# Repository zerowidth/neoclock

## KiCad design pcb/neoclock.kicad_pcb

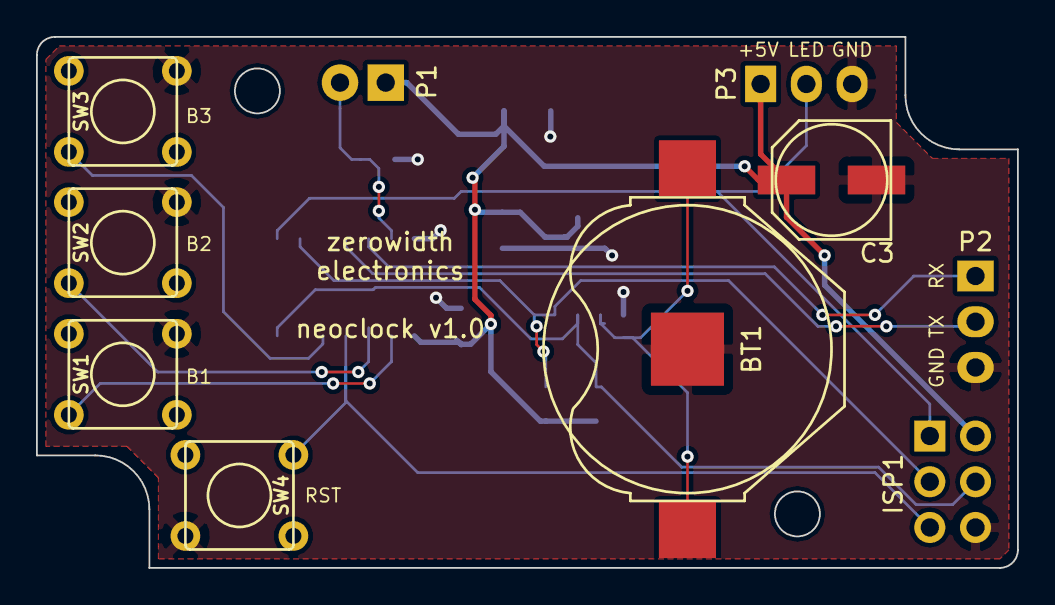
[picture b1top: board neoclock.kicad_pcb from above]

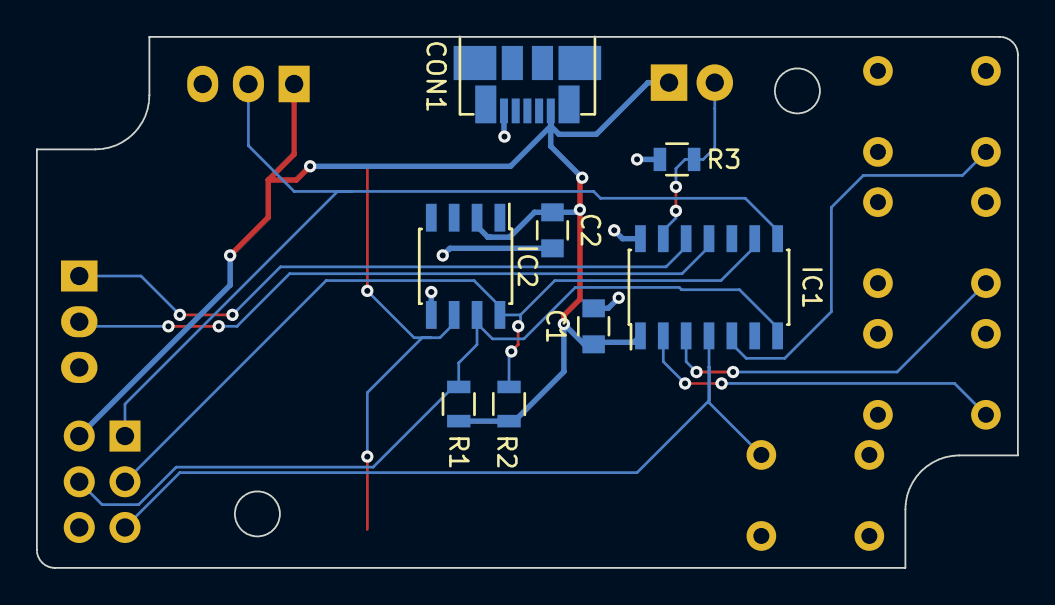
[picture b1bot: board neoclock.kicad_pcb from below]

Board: 2 copper layers, 54.5 x 29.5 mm, 18 parts (8 on the bottom side), 13 nets.

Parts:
BT1: CR1632; BAT_Keystone_3012TR_16mm
C1, C2: 0.1uF; C_0805
C3: 100uF; CP_Panasonic_SV_D
CON1: USB-MICRO-B; CONN_Molex_USB_Micro_SMT
IC1: ATTINY84-S; SOIC-14_3.9x8.7mm_Pitch1.27mm
IC2: DS3231MZ+; SOIC-8_3.9x4.9mm_Pitch1.27mm
ISP1: AVR-ISP-6; Pin_Header_Straight_2x03_Plain
P1: Photoresistor; Pin_Header_Straight_1x02_Plain
P2: Serial; Pin_Header_Straight_1x03_Plain
P3: NeoPixel Ring; Pin_Header_Straight_1x03_Plain
R1, R2, R3: 4.7k; R_0805
SW1: Button 1; BTN_E_Switch_TL1105
SW2: Button 2; BTN_E_Switch_TL1105
SW3: Button 3; BTN_E_Switch_TL1105
SW4: RESET; BTN_E_Switch_TL1105

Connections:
+5V: C1.1, C2.1, C3.1, CON1.1, IC1.1, IC2.2, ISP1.2, P1.1, P3.1, R1.1, R2.1
/BTN1: IC1.2, SW1.1
/BTN2: IC1.3, SW2.1
/BTN3: IC1.5, SW3.1
/LEDS: IC1.8, ISP1.1, P3.2
/LIGHT: IC1.13, P1.2, R3.1
/MOSI: IC1.7, IC2.7, ISP1.4, R1.2
/RST: IC1.4, ISP1.5, SW4.1
/RX: IC1.12, P2.1
/SCK: IC1.9, IC2.8, ISP1.3, R2.2
/TX: IC1.11, P2.2
/VBat: BT1.1, IC2.6
GND: BT1.2, C1.2, C2.2, C3.2, CON1.5, IC1.14, IC2.5, ISP1.6, P2.3, P3.3, R3.2, SW1.4, SW2.4, SW3.4, SW4.4

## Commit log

2015-02-12 Hello world: Blinking LED
    With Makefile from crosspack-avr
2015-02-13 Use attiny84a device
    The avr/io.h file has a more comprehensive set of constants e.g. timer
    control register bits. avrdude doesn't know about the -a variant though.
2015-02-13 `make all` compiles and flashes
    Also split out a `size` target for printing out the size
2015-02-13 PWM with FastPWM mode
2015-02-14 Import softuart library
    https://github.com/blalor/avr-softuart
2015-02-14 Get softuart demo up and running
2015-02-14 Remove -B argument from avrdude so it runs faster
    It might be needed again for flashing a new chip, though.
2015-02-14 Remove comments from makefile
2015-02-14 Add link-time optimization to build
    This cuts down the final build size by detecting undeclared static
    globals and more.
2015-02-14 Change suffix rule to prefix rule to build when headers change
    Previously, touching a header file wouldn't trigger a rebuild.
2015-02-14 Reintroduce PWM code
2015-02-14 Increase serial baud to 9600
2015-02-15 Fix dependency generation in Makefile
    -MMD generates local .d dependency files when compiling, and then the
    Makefile includes 'em to keep things updated.
2015-02-15 Generalize the PWM bits somewhat
2015-02-15 Move firmware into firmware directory
2015-02-15 MIT license
2015-02-22 Colorize avr-objdump output
2015-02-22 Compile .s files just in case
2015-02-22 asm to zero out a string of pixels
2015-02-22 asm loop to count 1 bits in a byte
2015-02-22 Fix debug output for avr-objdump
2015-02-22 Iterate over array of pixels in assembly
2015-02-23 Write pixel values to neopixels with carefully-timed asm
2015-02-23 Remove debugging bits
2015-02-23 Light up a 60-pixel ring
2015-02-23 Rotate the orange gradient
2015-02-23 Remove unused code
2015-02-25 Use constant pixels rather than function arg
2015-02-28 Import AVR310 example code
2015-02-28 Add definitions for the ATtiny84(A)
2015-02-28 Include USI lib in Makefile
2015-03-01 Print current time to serial
2015-03-01 Draw clock hands from the RTC
2015-03-01 Add a millisecond timer
    Accurate to 90% with WS2812B's interrupt disabling and a 15ms delay, or
    accurate to 95% without disabling interrupts. I assume any drift here is
    mainly because of the inaccuracy of the microcontroller's internal
    oscillator, but 90% is fine: the missing time can be spread out
    over the intervening time period for good enough animations.
2015-03-01 Support 32-bit integers in debug_int
2015-03-02 Stretch milliseconds to fit a full second
2015-03-03 Add serial make target
2015-03-07 Move serial and LED pins
2015-03-08 Echo in serial by default
2015-03-08 ADC with photoresistor, show light level on ring
2015-03-08 Draw animated clock face
    Including a pendulum, easing, and automatic light levels
2015-03-08 Use button to toggle pendulum
2015-03-09 Use buttons to set the time of day
2015-03-13 Add initial schematic
2015-03-13 Background fill for RTC chip, SOIC-8 package
2015-03-17 Update schematic, new lib with my own symbols
2015-03-17 Add footprints
    * Molex USB Micro SMT mount
    * Panasonic SV series electrolytic capacitor, size D
    * Keystone 3012TR 16mm coin cell battery holder
    * Plain versions of headers (no silk decoration)
2015-03-17 Use new symbols in schema
2015-03-17 Netlist and footprint assignment
2015-03-17 PCB design
2015-03-17 Ignore temp files
2015-03-17 Gerber files, oshpark packaging script
2015-03-17 Update USB connector so OSHPark doesn't get confused
    Having the silk hanging over the edge of the board meant the board size
    wasn’t calculated quite right, so in the interest of safety, replace the
    silk representing the board overhand with the Dwgs.User layer.
2015-03-17 Ignore the packaged project
2015-03-30 Enable brown-out detection at 4.3V
    Just in case, this should preserve flash/ecc when losing voltage
2015-03-30 `check` make target for quick connectivity testing
2015-03-30 Read PIXEL_OFFSET from Makefile, for easy override
2015-03-30 Add target markings for holes in the enclosure
    The triple-cross is for holes for the GL5528 photoresistor, and the
    single cross is for the hole for the LED ring.
